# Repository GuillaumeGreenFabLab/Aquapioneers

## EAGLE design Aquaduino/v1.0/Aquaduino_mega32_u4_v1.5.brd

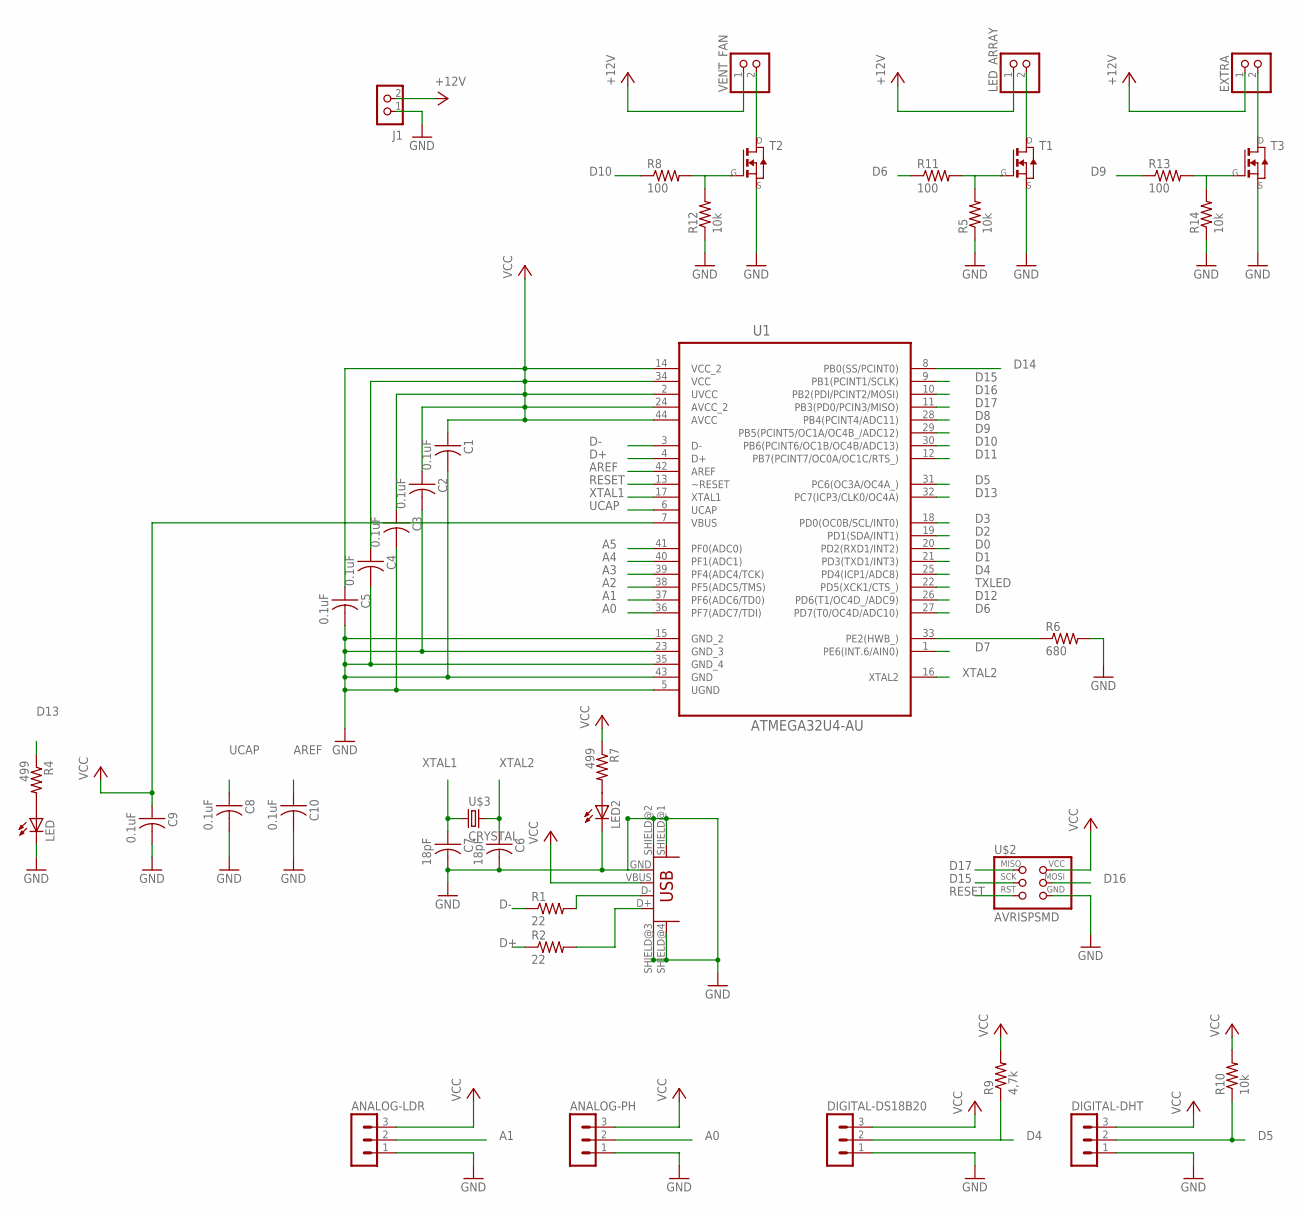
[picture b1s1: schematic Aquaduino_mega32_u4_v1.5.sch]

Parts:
ANALOG-LDR: MA03-1
ANALOG-PH: MA03-1
C1, C2, C3, C4, C5, C8, C9, C10: 0.1uF; C1206FAB
C6, C7: 18pF; C1206FAB
DIGITAL-DHT: MA03-1
DIGITAL-DS18B20: MA03-1
EXTRA: PINHD-1X2; 1X02
J1: CON_TERMINAL_BLOCK_02-5MM; TERMINAL_BLOCK_2P_5
LED, LED2: LED1206; 1206
LED_ARRAY: PINHD-1X2; 1X02
R1, R2: 22; R1206FAB
R4, R7: 499; 1206
R5, R10, R12, R14: 10k; R1206FAB
R6: 680; R1206FAB
R8, R11, R13: 100; R1206FAB
R9: 4,7k; R1206FAB
T1, T2, T3: NMOSFETTO252; TO252
U1: ATMEGA32U4-AU; QFP80P1200X1200X120-44N
U$1: USB_MINIB
U$2: AVRISPSMD; 2X03SMD
U$3: CRYSTAL; 2-SMD-5X3MM
VENT_FAN: PINHD-1X2; 1X02

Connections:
A0: ANALOG-PH.2, U1.36 (PF7(ADC7/TDI))
A1: ANALOG-LDR.2, U1.37 (PF6(ADC6/TD0))
A2: U1.38 (PF5(ADC5/TMS))
A3: U1.39 (PF4(ADC4/TCK))
A4: U1.40 (PF1(ADC1))
A5: U1.41 (PF0(ADC0))
AREF: C10.1, U1.42 (AREF)
D0: U1.20 (PD2(RXD1/INT2))
D1: U1.21 (PD3(TXD1/INT3))
D2: U1.19 (PD1(SDA/INT1))
D3: U1.18 (PD0(OC0B/SCL/INT0))
D4: DIGITAL-DS18B20.2, R9.1, U1.25 (PD4(ICP1/ADC8))
D5: DIGITAL-DHT.2, R10.1, U1.31 (PC6(OC3A/OC4A_))
D6: R11.1, U1.27 (PD7(T0/OC4D/ADC10))
D7: U1.1 (PE6(INT.6/AIN0))
D8: U1.28 (PB4(PCINT4/ADC11))
D9: R13.1, U1.29 (PB5(PCINT5/OC1A/OC4B_/ADC12))
D10: R8.1, U1.30 (PB6(PCINT6/OC1B/OC4B/ADC13))
D11: U1.12 (PB7(PCINT7/OC0A/OC1C/RTS_))
D12: U1.26 (PD6(T1/OC4D_/ADC9))
D13: R4.1, U1.32 (PC7(ICP3/CLK0/OC4A))
D14: U1.8 (PB0(SS/PCINT0))
D15: U1.9 (PB1(PCINT1/SCLK)), U$2.3 (SCK)
D16: U1.10 (PB2(PDI/PCINT2/MOSI)), U$2.4 (MOSI)
D17: U1.11 (PB3(PD0/PCIN3/MISO)), U$2.1 (MISO)
D+: R2.1, U1.4 (D+)
D-: R1.1, U1.3 (D-)
GND: ANALOG-LDR.1, ANALOG-PH.1, C1.2, C2.2, C3.2, C4.2, C5.2, C6.2, C7.2, C8.2, C9.2, C10.2, DIGITAL-DHT.1, DIGITAL-DS18B20.1, J1.1, LED.2 (C), LED2.2 (C), R5.1, R6.2, R12.1, R14.1, T1.2 (S), T2.2 (S), T3.2 (S), U1.5 (UGND), U1.15 (GND_2), U1.23 (GND_3), U1.35 (GND_4), U1.43 (GND), U$1.GND, U$1.SHIELD@1 (SHIELD), U$1.SHIELD@2 (SHIELD1), U$1.SHIELD@3 (SHIELD2), U$1.SHIELD@4 (SHIELD3), U$2.6 (GND)
unnamed: R1.2, U$1.D-
unnamed: R2.2, U$1.D+
unnamed: LED.1 (A), R4.2
unnamed: R8.2, R12.2, T2.1 (G)
unnamed: LED2.1 (A), R7.2
unnamed: T2.3 (D), VENT_FAN.2
unnamed: R13.2, R14.2, T3.1 (G)
unnamed: R5.2, R11.2, T1.1 (G)
unnamed: LED_ARRAY.2, T1.3 (D)
unnamed: EXTRA.2, T3.3 (D)
unnamed: R6.1, U1.33 (PE2(HWB_))
RESET: U1.13 (~RESET), U$2.5 (RST)
TXLED: U1.22 (PD5(XCK1/CTS_))
UCAP: C8.1, U1.6 (UCAP)
VCC: ANALOG-LDR.3, ANALOG-PH.3, C1.1, C2.1, C3.1, C4.1, C5.1, C9.1, DIGITAL-DHT.3, DIGITAL-DS18B20.3, EXTRA.1, J1.2, LED_ARRAY.1, R7.1, R9.2, R10.2, U1.2 (UVCC), U1.7 (VBUS), U1.14 (VCC_2), U1.24 (AVCC_2), U1.34 (VCC), U1.44 (AVCC), U$1.VBUS, U$2.2 (VCC), VENT_FAN.1
XTAL1: C7.1, U1.17 (XTAL1), U$3.P$1 (1)
XTAL2: C6.1, U1.16 (XTAL2), U$3.P$2 (2)

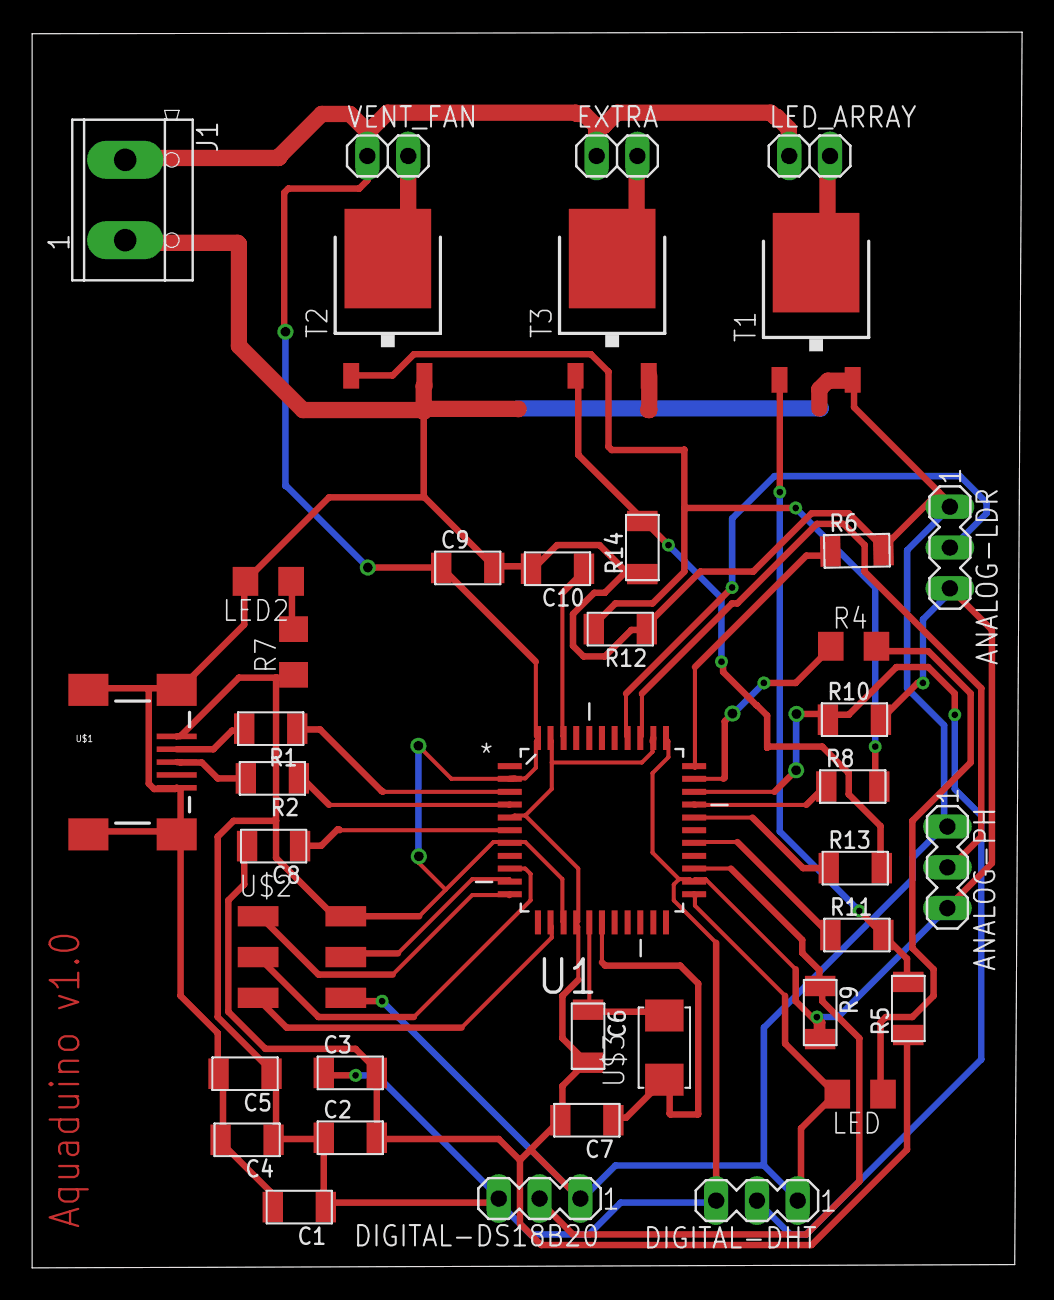
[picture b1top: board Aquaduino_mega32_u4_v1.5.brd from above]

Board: 2 copper layers, 61.6 x 77.0 mm, 40 parts (0 on the bottom side), 31 nets.

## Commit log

2016-04-26 first commit for aquapioneers
2016-04-26 FabLab compatible Arduino for Aquaponics v1.1
    **Electronics Enclosure**
    Aquaduino v1.0 has been designed for
    - 2 digital inputs (i.e. water T°C + & air T°C & humidity)
    - 2 analog inputs (i.e. pH probe + LDR)
    - 3 outputs (i.e. 1-LED array, 2- Vent Fan, 3- extra)
    Microcontroller: ATMEGA32U4
2019-07-11 Set theme jekyll-theme-cayman
